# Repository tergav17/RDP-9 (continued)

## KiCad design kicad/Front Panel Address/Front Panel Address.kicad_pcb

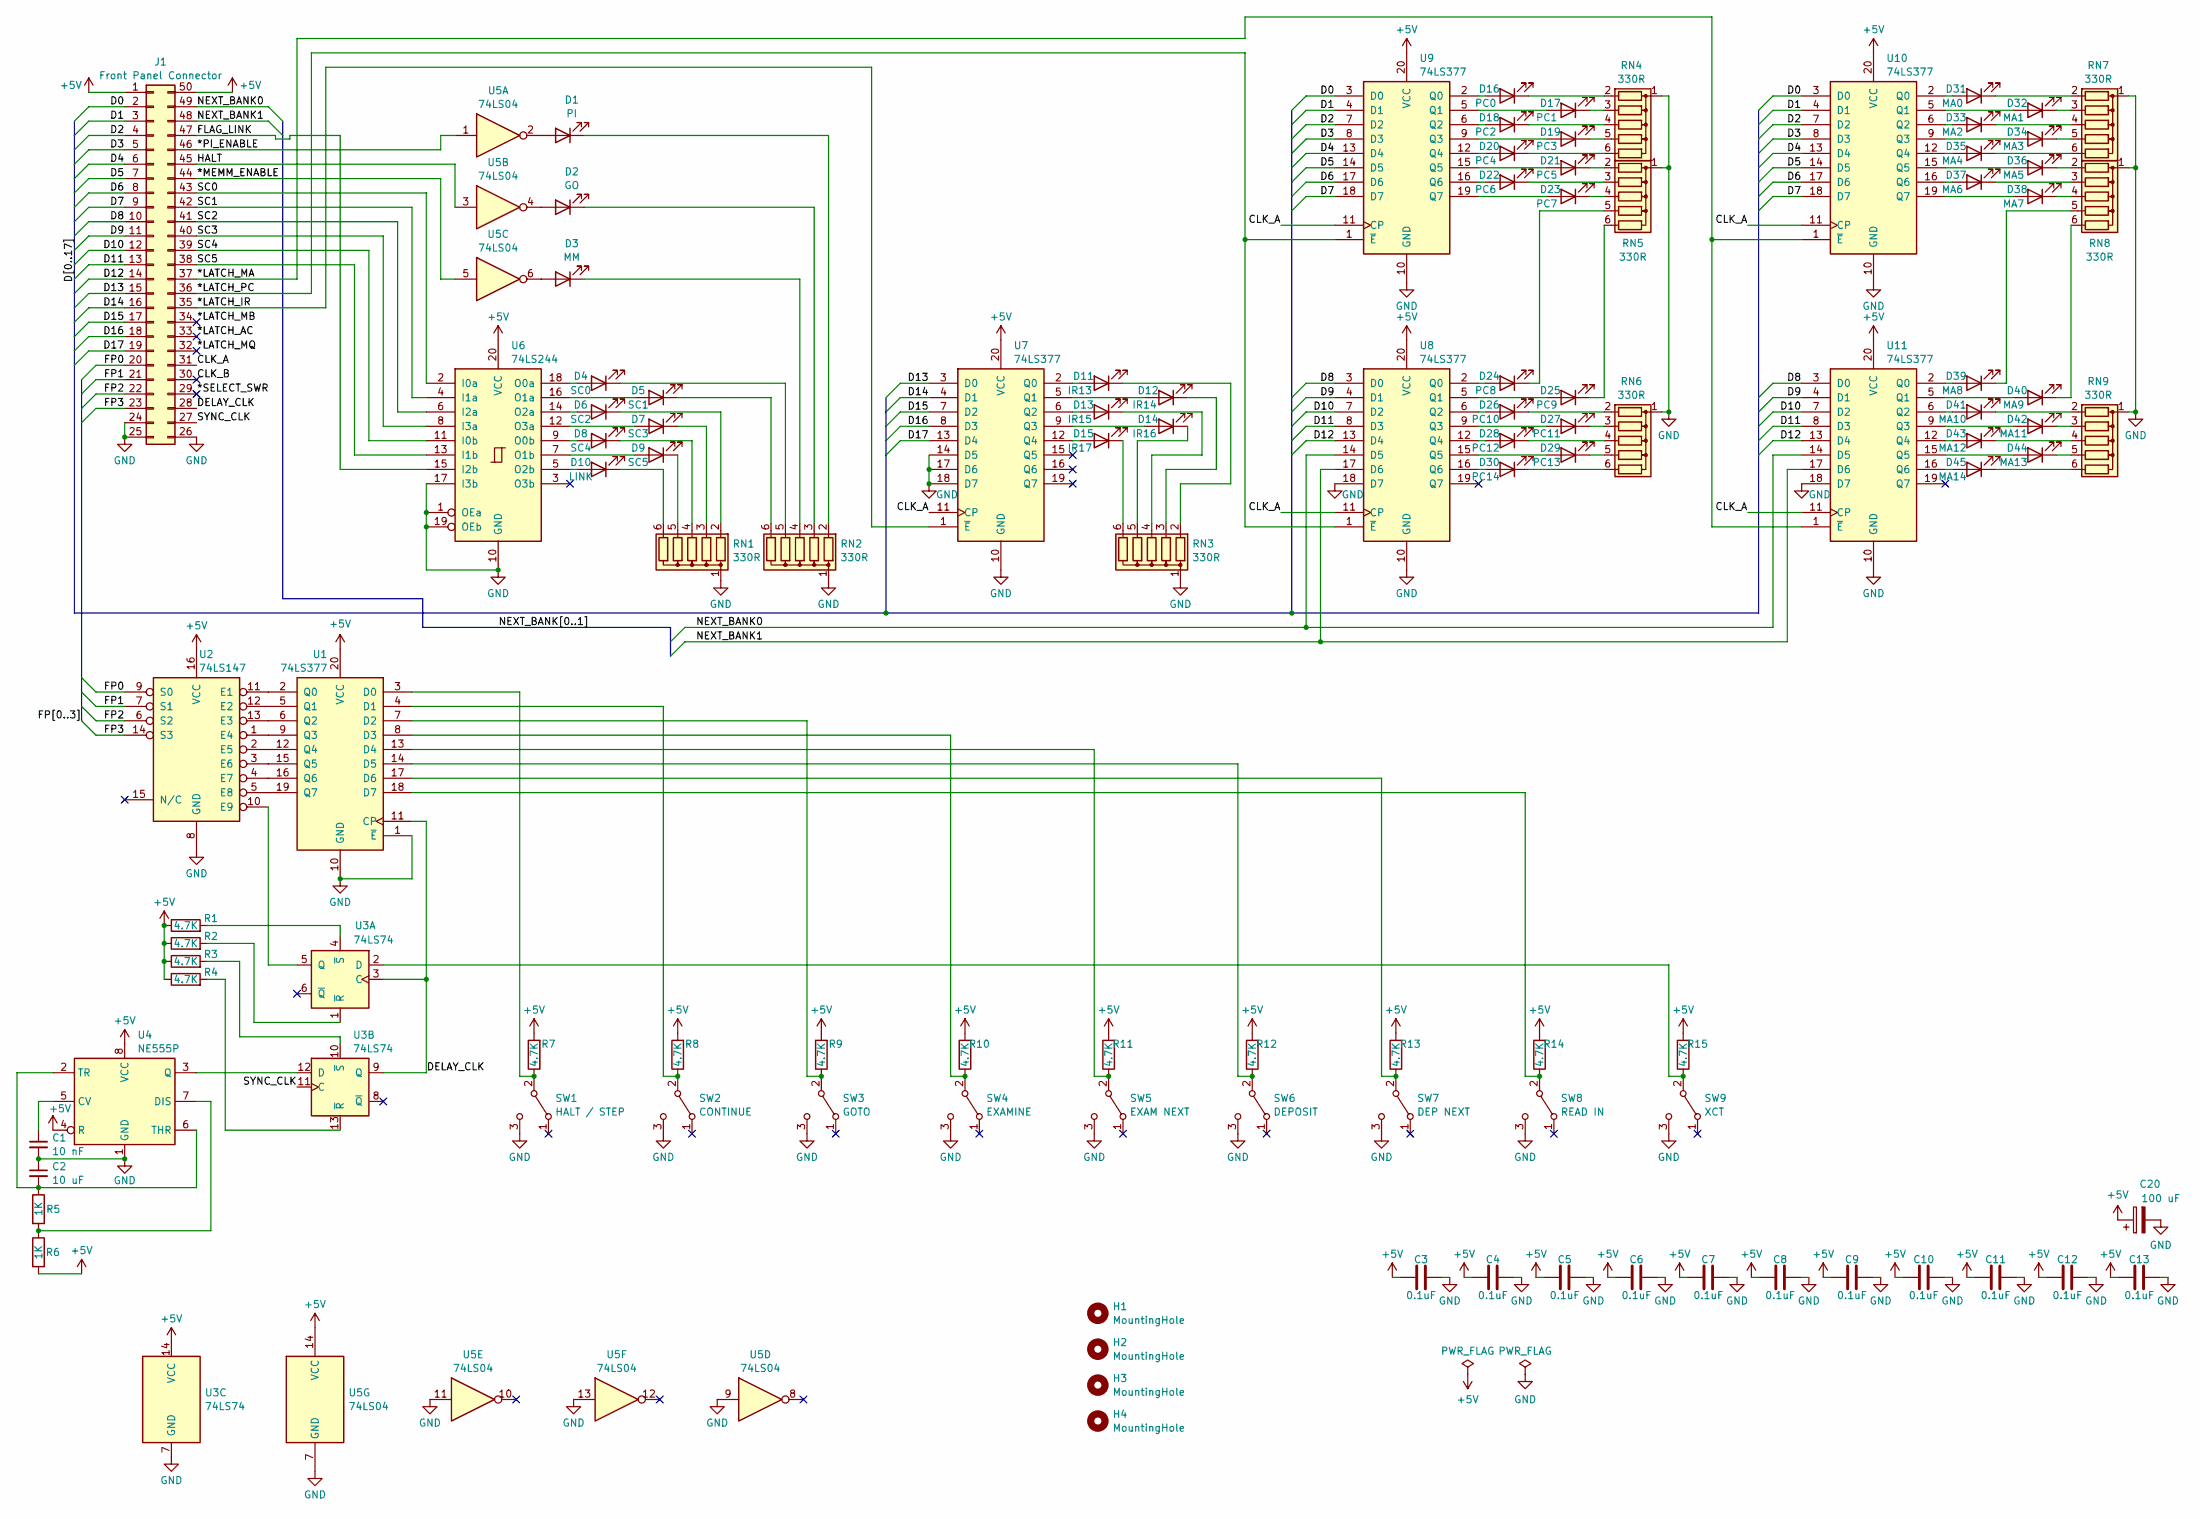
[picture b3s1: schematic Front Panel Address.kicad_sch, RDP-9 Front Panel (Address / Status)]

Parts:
C1: 10 nF; C_Disc_D5.0mm_W2.5mm_P5.00mm
C2: 10 uF; C_Disc_D5.0mm_W2.5mm_P5.00mm
C3, C4, C5, C6, C7, C8, C9, C10, C11, C12, C13: 0.1uF; C_Disc_D5.0mm_W2.5mm_P5.00mm
C20: 100 uF; CP_Radial_D6.3mm_P2.50mm
D1: PI; LED_D5.0mm
D2: GO; LED_D5.0mm
D3: MM; LED_D5.0mm
D4: SC0; LED_D5.0mm
D5: SC1; LED_D5.0mm
D6: SC2; LED_D5.0mm
D7: SC3; LED_D5.0mm
D8: SC4; LED_D5.0mm
D9: SC5; LED_D5.0mm
D10: LINK; LED_D5.0mm
D11: IR13; LED_D5.0mm
D12: IR14; LED_D5.0mm
D13: IR15; LED_D5.0mm
D14: IR16; LED_D5.0mm
D15: IR17; LED_D5.0mm
D16: PC0; LED_D5.0mm
D17: PC1; LED_D5.0mm
D18: PC2; LED_D5.0mm
D19: PC3; LED_D5.0mm
D20: PC4; LED_D5.0mm
D21: PC5; LED_D5.0mm
D22: PC6; LED_D5.0mm
D23: PC7; LED_D5.0mm
D24: PC8; LED_D5.0mm
D25: PC9; LED_D5.0mm
D26: PC10; LED_D5.0mm
D27: PC11; LED_D5.0mm
D28: PC12; LED_D5.0mm
D29: PC13; LED_D5.0mm
D30: PC14; LED_D5.0mm
D31: MA0; LED_D5.0mm
D32: MA1; LED_D5.0mm
D33: MA2; LED_D5.0mm
D34: MA3; LED_D5.0mm
D35: MA4; LED_D5.0mm
D36: MA5; LED_D5.0mm
D37: MA6; LED_D5.0mm
D38: MA7; LED_D5.0mm
D39: MA8; LED_D5.0mm
D40: MA9; LED_D5.0mm
D41: MA10; LED_D5.0mm
D42: MA11; LED_D5.0mm
D43: MA12; LED_D5.0mm
D44: MA13; LED_D5.0mm
D45: MA14; LED_D5.0mm
H1, H2, H3, H4: MountingHole; MountingHole_2.2mm_M2_Pad
J1: Front Panel Connector; IDC-Header_2x25_P2.54mm_Vertical
R1, R2, R3, R4, R7, R8, R9, R10, R11, R12, R13, R14, R15: 4.7K; R_Axial_DIN0207_L6.3mm_D2.5mm_P7.62mm_Horizontal
R5, R6: 1K; R_Axial_DIN0207_L6.3mm_D2.5mm_P7.62mm_Horizontal
RN1, RN2, RN3, RN4, RN5, RN6, RN7, RN8, RN9: 330R; R_Array_SIP6
SW1: HALT / STEP; MTS-102
SW2: CONTINUE; MTS-102
SW3: GOTO; MTS-102
SW4: EXAMINE; MTS-102
SW5: EXAM NEXT; MTS-102
SW6: DEPOSIT; MTS-102
SW7: DEP NEXT; MTS-102
SW8: READ IN; MTS-102
SW9: XCT; MTS-102
U1, U7, U8, U9, U10, U11: 74LS377; DIP-20_W7.62mm
U2: 74LS147; DIP-16_W7.62mm
U3: 74LS74; DIP-14_W7.62mm
U4: NE555P; DIP-8_W7.62mm
U5: 74LS04; DIP-14_W7.62mm
U6: 74LS244; DIP-20_W7.62mm

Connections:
+5V: C3.1, C4.1, C5.1, C6.1, C7.1, C8.1, C9.1, C10.1, C11.1, C12.1, C13.1, J1.1, J1.50, R1.1, R2.1, R3.1, R4.1, R6.2, R7.2, R8.2, R9.2, R10.2, R11.2, R12.2, R13.2, R14.2, R15.2, U1.20 (VCC), U2.16 (VCC), U3.14 (VCC), U4.4 (R), U4.8 (VCC), U5.14 (VCC), U6.20 (VCC), U7.20 (VCC), U8.20 (VCC), U9.20 (VCC), U10.20 (VCC), U11.20 (VCC); also elsewhere on the board
/*LATCH_AC: J1.33
/*LATCH_IR: J1.35, U7.1 (~E)
/*LATCH_MA: J1.37, U10.1 (~E), U11.1 (~E)
/*LATCH_MB: J1.34
/*LATCH_MQ: J1.32
/*LATCH_PC: J1.36, U8.1 (~E), U9.1 (~E)
/*MEMM_ENABLE: J1.44, U5.5
/*PI_ENABLE: J1.46, U5.1
/*SELECT_SWR: J1.29
/CLK_A: J1.31, U7.11 (CP), U8.11 (CP), U9.11 (CP), U10.11 (CP), U11.11 (CP)
/CLK_B: J1.30
/D0: J1.2, U9.3 (D0), U10.3 (D0)
/D1: J1.3, U9.4 (D1), U10.4 (D1)
/D2: J1.4, U9.7 (D2), U10.7 (D2)
/D3: J1.5, U9.8 (D3), U10.8 (D3)
/D4: J1.6, U9.13 (D4), U10.13 (D4)
/D5: J1.7, U9.14 (D5), U10.14 (D5)
/D6: J1.8, U9.17 (D6), U10.17 (D6)
/D7: J1.9, U9.18 (D7), U10.18 (D7)
/D8: J1.10, U8.3 (D0), U11.3 (D0)
/D9: J1.11, U8.4 (D1), U11.4 (D1)
/D10: J1.12, U8.7 (D2), U11.7 (D2)
/D11: J1.13, U8.8 (D3), U11.8 (D3)
/D12: J1.14, U8.13 (D4), U11.13 (D4)
/D13: J1.15, U7.3 (D0)
/D14: J1.16, U7.4 (D1)
/D15: J1.17, U7.7 (D2)
/D16: J1.18, U7.8 (D3)
/D17: J1.19, U7.13 (D4)
/DELAY_CLK: J1.28, U1.11 (CP), U3.3 (C), U3.9 (Q)
/FLAG_LINK: J1.47, U6.15 (I2b)
/FP0: J1.20, U2.9 (S0)
/FP1: J1.21, U2.7 (S1)
/FP2: J1.22, U2.6 (S2)
/FP3: J1.23, U2.14 (S3)
/HALT: J1.45, U5.3
/NEXT_BANK0: J1.49, U8.14 (D5), U11.14 (D5)
/NEXT_BANK1: J1.48, U8.17 (D6), U11.17 (D6)
/SC0: J1.43, U6.2 (I0a)
/SC1: J1.42, U6.4 (I1a)
/SC2: J1.41, U6.6 (I2a)
/SC3: J1.40, U6.8 (I3a)
/SC4: J1.39, U6.11 (I0b)
/SC5: J1.38, U6.13 (I1b)
/SYNC_CLK: J1.27, U3.11 (C)
GND: C1.2, C2.1, C3.2, C4.2, C5.2, C6.2, C7.2, C8.2, C9.2, C10.2, C11.2, C12.2, C13.2, J1.24, J1.25, J1.26, RN1.1 (common), RN2.1 (common), RN3.1 (common), RN4.1 (common), RN5.1 (common), RN6.1 (common), RN7.1 (common), RN8.1 (common), RN9.1 (common), SW1.3 (C), SW2.3 (C), SW3.3 (C), SW4.3 (C), SW5.3 (C), SW6.3 (C), SW7.3 (C), SW8.3 (C), SW9.3 (C), U1.1 (~E), U1.10 (GND), U2.8 (GND), U3.7 (GND), U4.1 (GND), U5.7 (GND), U5.9, U5.11, U5.13, U6.1 (OEa), U6.10 (GND), U6.17 (I3b), U6.19 (OEb), U7.10 (GND), U7.14 (D5), U7.17 (D6), U7.18 (D7), U8.10 (GND), U8.18 (D7), U9.10 (GND), U10.10 (GND), U11.10 (GND), U11.18 (D7); also elsewhere on the board
unnamed: D1.2 (A), U5.2
unnamed: D1.1 (K), RN2.2 (R1)
unnamed: D2.2 (A), U5.4
unnamed: D2.1 (K), RN2.3 (R2)
unnamed: D3.2 (A), U5.6
unnamed: D3.1 (K), RN2.4 (R3)
unnamed: D4.2 (A), U6.18 (O0a)
unnamed: D4.1 (K), RN2.5 (R4)
unnamed: D5.2 (A), U6.16 (O1a)
unnamed: D5.1 (K), RN2.6 (R5)
unnamed: D6.2 (A), U6.14 (O2a)
unnamed: D6.1 (K), RN1.2 (R1)
unnamed: D7.2 (A), U6.12 (O3a)
unnamed: D7.1 (K), RN1.3 (R2)
unnamed: D8.2 (A), U6.9 (O0b)
unnamed: D8.1 (K), RN1.4 (R3)
unnamed: D9.2 (A), U6.7 (O1b)
unnamed: D9.1 (K), RN1.5 (R4)
unnamed: D10.2 (A), U6.5 (O2b)
unnamed: D10.1 (K), RN1.6 (R5)
unnamed: D11.2 (A), U7.2 (Q0)
unnamed: D11.1 (K), RN3.2 (R1)
unnamed: D12.2 (A), U7.5 (Q1)
unnamed: D12.1 (K), RN3.3 (R2)
unnamed: D13.2 (A), U7.6 (Q2)
unnamed: D13.1 (K), RN3.4 (R3)
unnamed: D14.2 (A), U7.9 (Q3)
unnamed: D14.1 (K), RN3.5 (R4)
unnamed: D15.2 (A), U7.12 (Q4)
unnamed: D15.1 (K), RN3.6 (R5)
unnamed: D16.2 (A), U9.2 (Q0)
unnamed: D16.1 (K), RN4.2 (R1)
unnamed: D17.2 (A), U9.5 (Q1)
unnamed: D17.1 (K), RN4.3 (R2)
unnamed: D18.2 (A), U9.6 (Q2)
unnamed: D18.1 (K), RN4.4 (R3)
unnamed: D19.2 (A), U9.9 (Q3)
unnamed: D19.1 (K), RN4.5 (R4)
unnamed: D20.2 (A), U9.12 (Q4)
unnamed: D20.1 (K), RN4.6 (R5)
unnamed: D21.2 (A), U9.15 (Q5)
unnamed: D21.1 (K), RN5.2 (R1)
unnamed: D22.2 (A), U9.16 (Q6)
unnamed: D22.1 (K), RN5.3 (R2)
unnamed: D23.2 (A), U9.19 (Q7)
unnamed: D23.1 (K), RN5.4 (R3)
unnamed: D24.2 (A), U8.2 (Q0)
unnamed: D24.1 (K), RN5.5 (R4)
unnamed: D25.2 (A), U8.5 (Q1)
unnamed: D25.1 (K), RN5.6 (R5)
unnamed: D26.2 (A), U8.6 (Q2)
unnamed: D26.1 (K), RN6.2 (R1)
unnamed: D27.2 (A), U8.9 (Q3)
unnamed: D27.1 (K), RN6.3 (R2)
unnamed: D28.2 (A), U8.12 (Q4)
unnamed: D28.1 (K), RN6.4 (R3)
unnamed: D29.2 (A), U8.15 (Q5)
unnamed: D29.1 (K), RN6.5 (R4)
unnamed: D30.2 (A), U8.16 (Q6)
unnamed: D30.1 (K), RN6.6 (R5)
unnamed: D31.2 (A), U10.2 (Q0)
unnamed: D31.1 (K), RN7.2 (R1)
unnamed: D32.2 (A), U10.5 (Q1)
unnamed: D32.1 (K), RN7.3 (R2)
unnamed: D33.2 (A), U10.6 (Q2)
unnamed: D33.1 (K), RN7.4 (R3)
unnamed: D34.2 (A), U10.9 (Q3)
unnamed: D34.1 (K), RN7.5 (R4)
unnamed: D35.2 (A), U10.12 (Q4)
unnamed: D35.1 (K), RN7.6 (R5)
unnamed: D36.2 (A), U10.15 (Q5)
unnamed: D36.1 (K), RN8.2 (R1)
unnamed: D37.2 (A), U10.16 (Q6)
unnamed: D37.1 (K), RN8.3 (R2)
unnamed: D38.2 (A), U10.19 (Q7)
unnamed: D38.1 (K), RN8.4 (R3)
unnamed: D39.2 (A), U11.2 (Q0)
unnamed: D39.1 (K), RN8.5 (R4)
unnamed: D40.2 (A), U11.5 (Q1)
unnamed: D40.1 (K), RN8.6 (R5)
unnamed: D41.2 (A), U11.6 (Q2)
unnamed: D41.1 (K), RN9.2 (R1)
unnamed: D42.2 (A), U11.9 (Q3)
unnamed: D42.1 (K), RN9.3 (R2)
unnamed: D43.2 (A), U11.12 (Q4)
unnamed: D43.1 (K), RN9.4 (R3)
unnamed: D44.2 (A), U11.15 (Q5)
unnamed: D44.1 (K), RN9.5 (R4)
unnamed: D45.2 (A), U11.16 (Q6)
unnamed: D45.1 (K), RN9.6 (R5)
unnamed: R7.1, SW1.2 (B), U1.3 (D0)
unnamed: R8.1, SW2.2 (B), U1.4 (D1)
unnamed: R9.1, SW3.2 (B), U1.7 (D2)
unnamed: R10.1, SW4.2 (B), U1.8 (D3)
unnamed: R11.1, SW5.2 (B), U1.13 (D4)
unnamed: R12.1, SW6.2 (B), U1.14 (D5)
unnamed: R13.1, SW7.2 (B), U1.17 (D6)
unnamed: R14.1, SW8.2 (B), U1.18 (D7)
unnamed: R15.1, SW9.2 (B), U3.2 (D)
unnamed: U1.2 (Q0), U2.11 (E1)
unnamed: U1.5 (Q1), U2.12 (E2)
unnamed: U1.6 (Q2), U2.13 (E3)
unnamed: U1.9 (Q3), U2.1 (E4)
unnamed: U1.12 (Q4), U2.2 (E5)
unnamed: U1.15 (Q5), U2.3 (E6)
unnamed: U1.16 (Q6), U2.4 (E7)
unnamed: U1.19 (Q7), U2.5 (E8)
unnamed: U2.10 (E9), U3.5 (Q)
unnamed: R2.2, U3.1 (~R)
unnamed: R1.2, U3.4 (~S)
unnamed: U3.12 (D), U4.3 (Q)
unnamed: R4.2, U3.13 (~R)
unnamed: R3.2, U3.10 (~S)
unnamed: C1.1, U4.5 (CV)
unnamed: R5.2, R6.1, U4.7 (DIS)
unnamed: C2.2, R5.1, U4.2 (TR), U4.6 (THR)

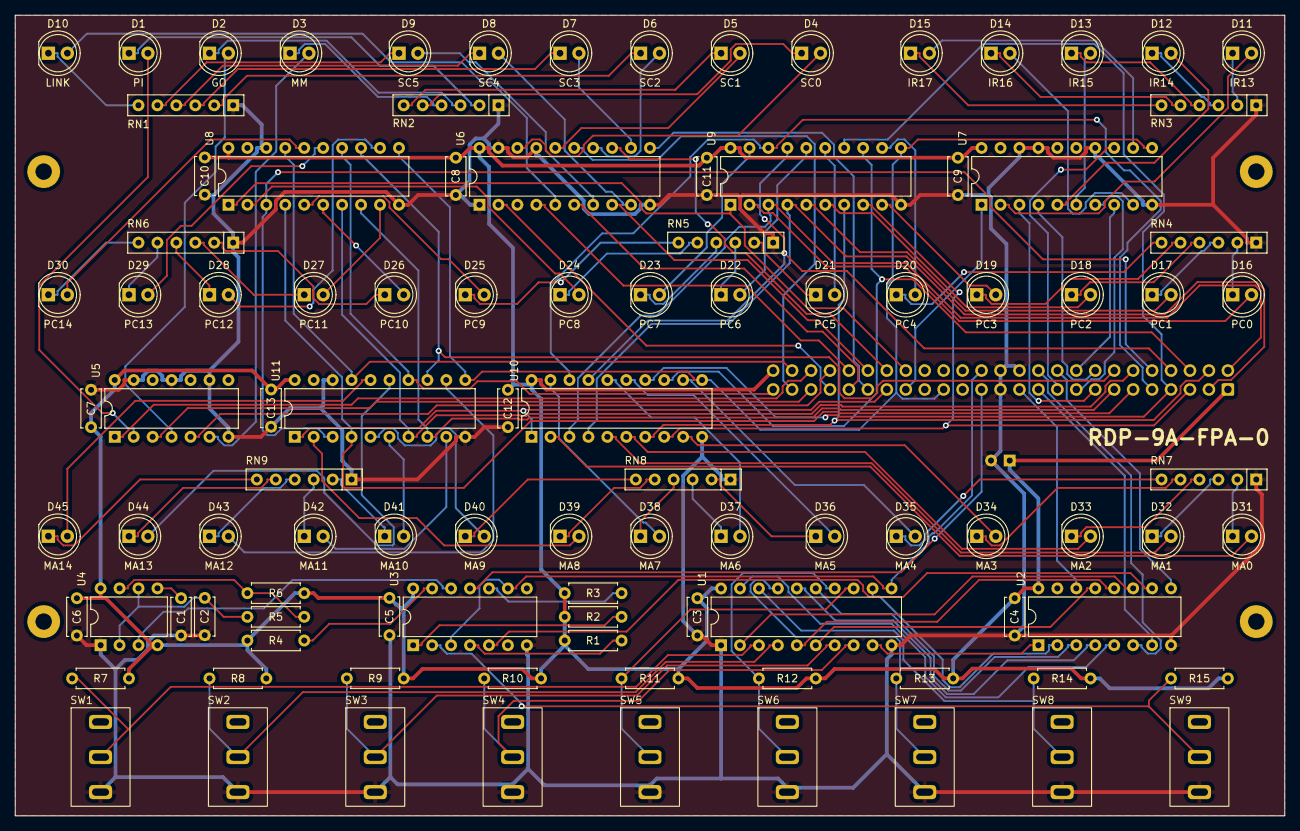
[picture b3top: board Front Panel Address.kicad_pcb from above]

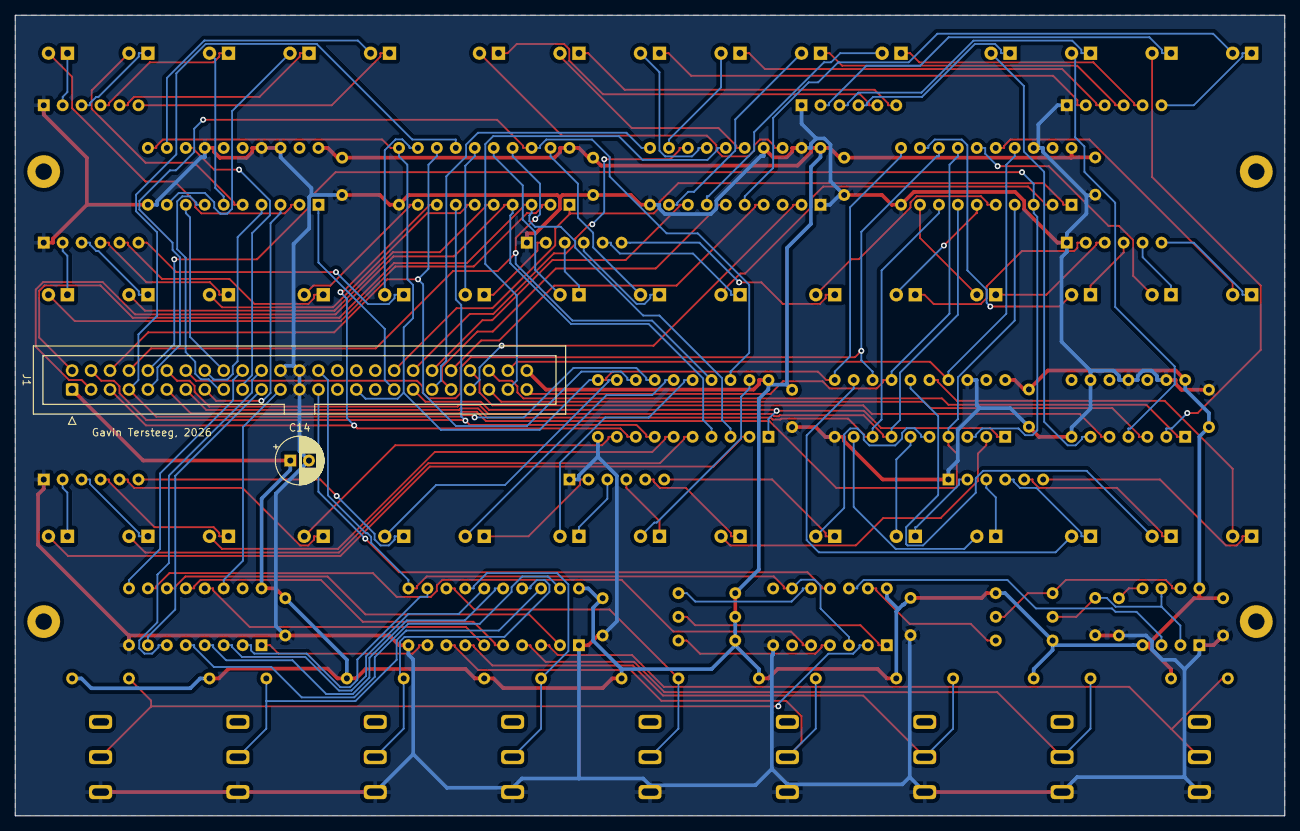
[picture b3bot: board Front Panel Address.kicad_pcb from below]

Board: 2 copper layers, 170.2 x 107.3 mm, 108 parts (2 on the bottom side), 158 nets.

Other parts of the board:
C14: 100 uF; CP_Radial_D6.3mm_P2.50mm

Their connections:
+5V: C14.1; also elsewhere on the board
GND: C14.2; also elsewhere on the board
